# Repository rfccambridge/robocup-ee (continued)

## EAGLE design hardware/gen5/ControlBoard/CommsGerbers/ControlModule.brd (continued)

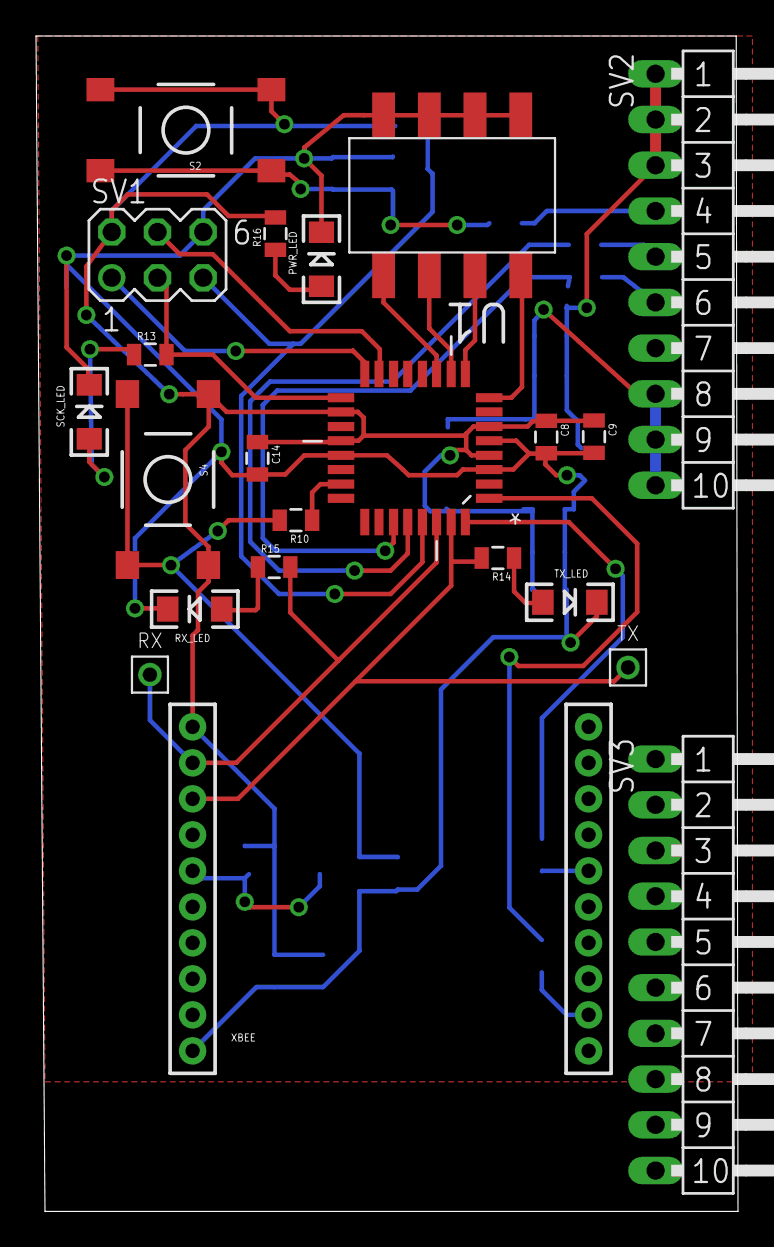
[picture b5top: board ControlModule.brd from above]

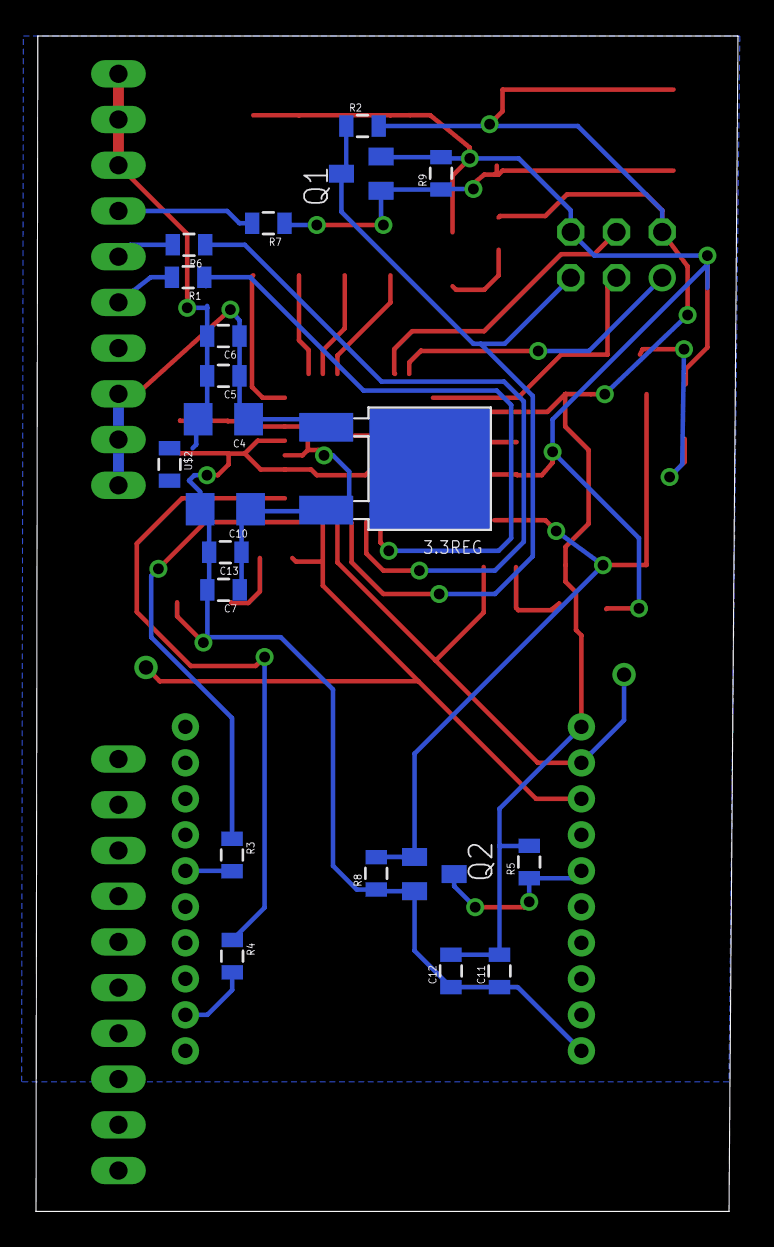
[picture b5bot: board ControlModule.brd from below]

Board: 2 copper layers, 39.0 x 65.3 mm, 44 parts (21 on the bottom side), 31 nets.

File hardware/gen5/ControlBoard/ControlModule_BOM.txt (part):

Partlist exported from C:/Users/joncr_000/robocup/robocup-ee/hardware/gen5/ControlBoard/ControlModule.sch at 12/26/2016 15:41:58

Part    Value         Device           Package               Description                                             MF MPN           OC_FARNELL OC_NEWARK PACKAGE PROD_ID    SUPPLIER VALUE        
3.3REG  3.3REG1AREG   3.3REG1AREG      DPAK                                                                                                                                                         
C4      47uF          CAP1206          1206                  Capacitor                                                                                                                              
C5      1uF           CAP0805          0805                  Capacitor                                                                                                                              
C6      0.01uF        CAP0805          0805                  Capacitor                                                                                                                              
C7      0.01uF        CAP0805          0805                  Capacitor                                                                                                                              
C8      10uF          CAP0805          0805                  Capacitor                                                                                                                              
C9      0.1uF         CAP0805          0805                  Capacitor                                                                                                                              
C10     47uF          CAP1206          1206                  Capacitor                                                                                                                              
C11     0.01uF        CAP0805          0805                  Capacitor                                                                                                                              
C12     1uF           CAP0805          0805                  Capacitor                                                                                                                              
C13     1uF           CAP0805          0805                  Capacitor                                                                                                                              
C14     0.1uF         CAP0805          0805                  Capacitor                                                                                                                              
FRAME1  FRAME-LETTER  FRAME-LETTER     CREATIVE_COMMONS      Schematic Frame                                                                                                                        
PWR_LED               LED1206          LED-1206              LEDs                                                                                                                                   
Q1      BSS123        BSS123           SOT23                 N-CHANNEL MOS FET                                                                                                                      
Q2      BSS123        BSS123           SOT23                 N-CHANNEL MOS FET                                                                                                                      
R1      100           RESISTOR0805-RES 0805                  Resistor                                                                                                                               
R2      10k           RESISTOR0805-RES 0805                  Resistor                                                                                                                               
R3      0             RESISTOR0805-RES 0805                  Resistor                                                                                                                               
R4      0             RESISTOR0805-RES 0805                  Resistor                                                                                                                               
R5      10k           RESISTOR0805-RES 0805                  Resistor                                                                                                                               
R6      100           RESISTOR0805-RES 0805                  Resistor                                                                                                                               
R7      100           RESISTOR0805-RES 0805                  Resistor                                                                                                                               
R8      10k           RESISTOR0805-RES 0805                  Resistor                                                                                                                               
R9      10k           RESISTOR0805-RES 0805                  Resistor                                                                                                                               
R10     100           RESISTOR0805-RES 0805                  Resistor                                                                                                                               
R13     1k            RESISTOR0805-RES 0805                  Resistor                                                                                                                               
R14     1k            RESISTOR0805-RES 0805                  Resistor                                                                                                                               
R15     1k            RESISTOR0805-RES 0805                  Resistor                                                                                                                               
R16     1k            RESISTOR0805-RES 0805                  Resistor                                                                                                                               
RX      TEST_PT       TEST_PT          TESTING_PT            Testing Point                                                                                                                          
RX_LED                LED1206          LED-1206              LEDs                                                                                                                                   
S2      TAC_SWITCHSMD TAC_SWITCHSMD    TACTILE-SWITCH-SMD    Momentary Switch                                                                                      SWCH-08247          TAC_SWITCHSMD
S4      TAC_SWITCHSMD TAC_SWITCHSMD    TACTILE-SWITCH-SMD    Momentary Switch                                                                                      SWCH-08247          TAC_SWITCHSMD
SCK_LED               LED1206          LED-1206              LEDs                                                                                                                                   
SV1     ICSP          MA03-2           MA03-2                PIN HEADER                                                               unknown    unknown                                            
SV2                   MA10-1W          MA10-1W               PIN HEADER                                                               unknown    unknown                                            
SV3                   MA10-1W          MA10-1W               PIN HEADER                                                               unknown    unknown                                            
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
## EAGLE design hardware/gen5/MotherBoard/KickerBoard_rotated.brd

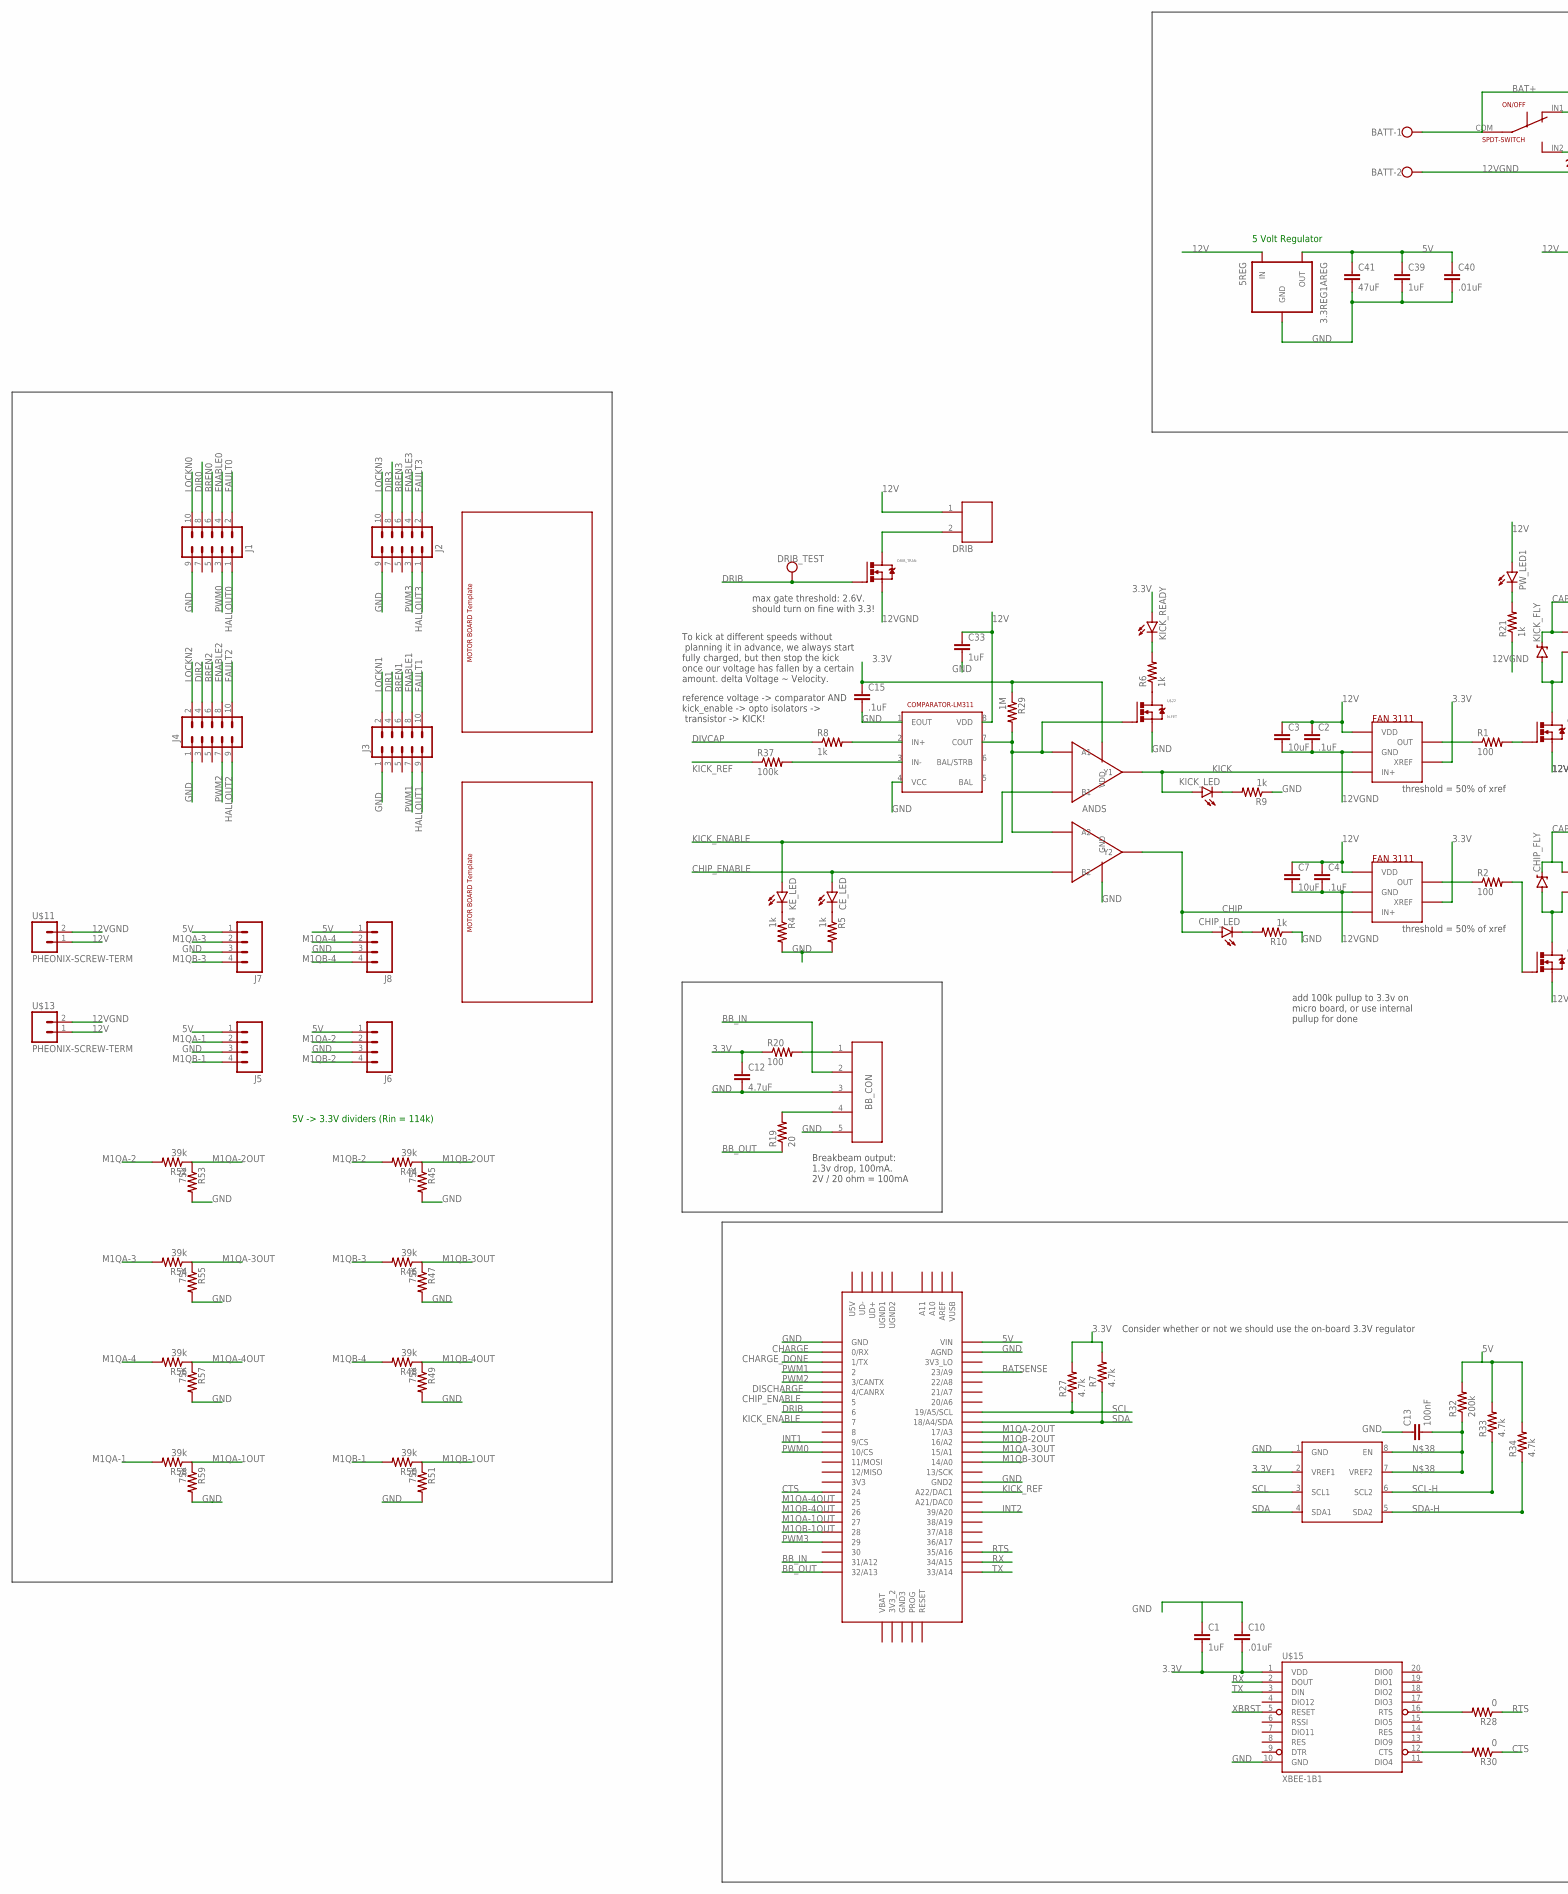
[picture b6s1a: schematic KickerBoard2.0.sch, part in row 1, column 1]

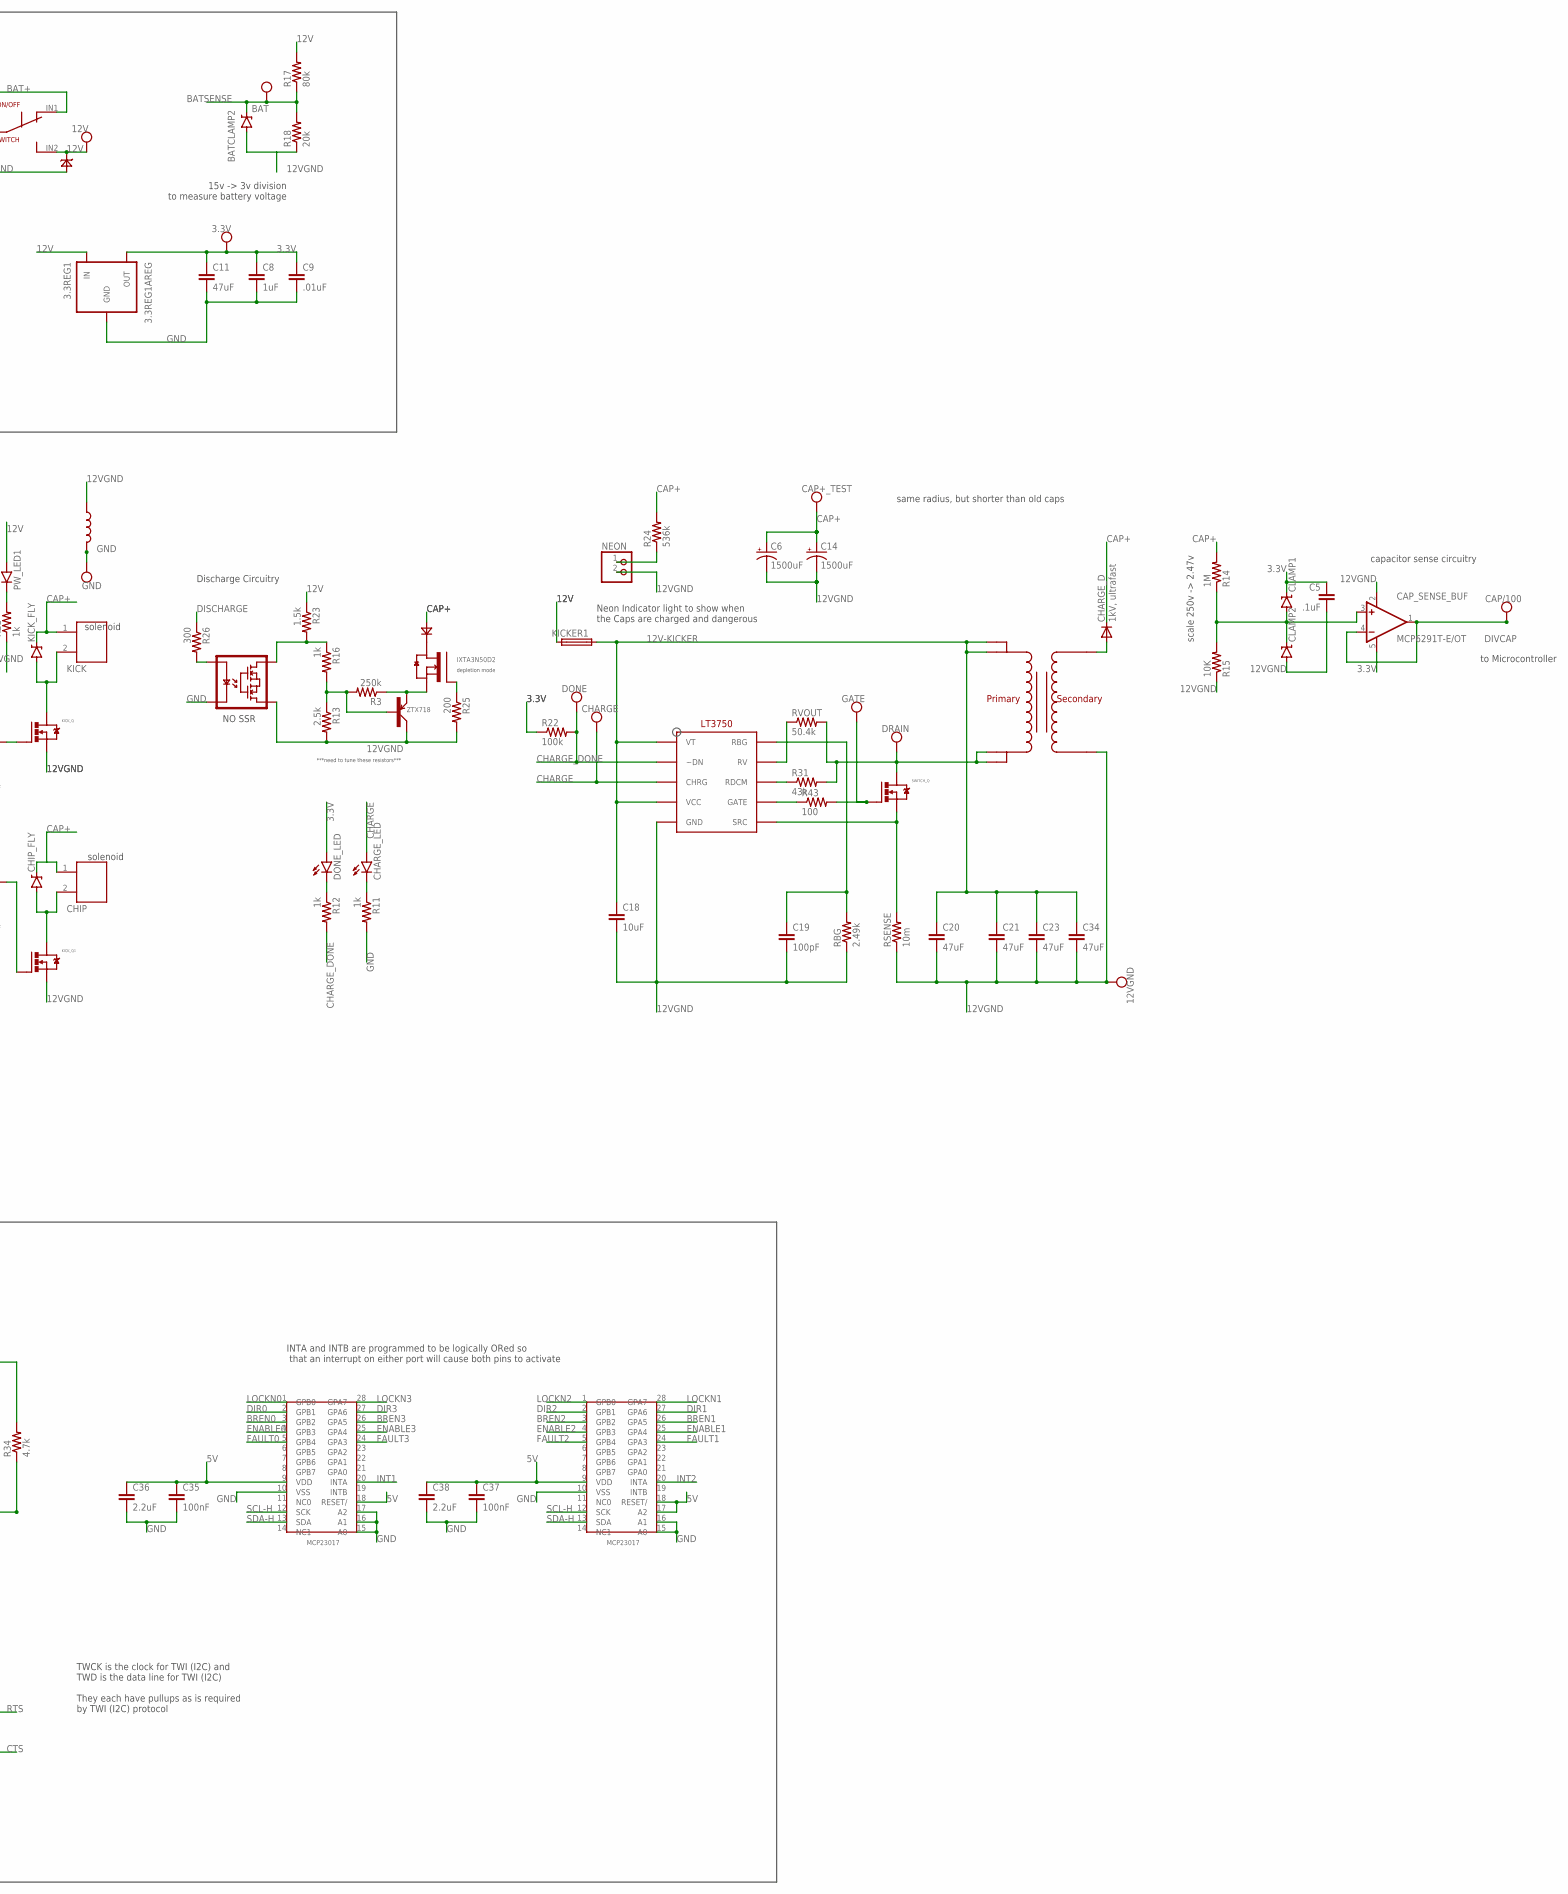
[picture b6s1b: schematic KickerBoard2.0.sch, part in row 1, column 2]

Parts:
3.3REG1, 5REG: 3.3REG1AREG; DPAK
3.3V, 12V, 12VGND: TEST_PT; TESTING_PT
ANDS: AND-DUAL; TSSOP8
BAT: TEST_PT; TESTING_PT
BATCLAMP2: DIODE-ZENERDO214AC; DO214AC
BATT: W237-102
BB_CON: JST-5; JST-5-2MM
C1, C33: 1uF; 1206
C2, C4: .1uF; 1206
C3, C7: 10uF; 1206
C5, C15: .1uF; 0805
C6, C14: 1500uF; EB35D
C8, C39: 1uF; 0805
C9, C40: .01uF; 0805
C10: .01uF; 1206
C11, C20, C21, C23, C34, C41: 47uF; 1206
C12: 4.7uF; 0805
C13, C35, C37: 100nF; 0805
C18: 10uF; 0805
C19: 100pF; 0805
C36, C38: 2.2uF; 0805
CAP+_TEST: TEST_PT; TESTING_PT
CAP/100: TEST_PT; TESTING_PT
CAP_SENSE_BUF: MCP6291T-E/OT; SOT23-5
CE_LED: LED1206; LED-1206
CHARGE: TEST_PT; TESTING_PT
CHARGE_D: 1kV, ultrafast; DO214AC
CHARGE_LED: LED1206; LED-1206
CHARGE_U: LT3750; 10-MSOP
CHIP: JST-22MM; JST-2-2MM
CHIP_FLY: DIODE-ZENERDO214AB; DO214AB
CHIP_LED: LED1206; LED-1206
CLAMP1, CLAMP2: DIODE-ZENERDO214AC; DO214AC
DONE: TEST_PT; TESTING_PT
DONE_LED: LED1206; LED-1206
DRAIN: TEST_PT; TESTING_PT
DRIB: JST-22MM; JST-2-2MM
DRIB_TEST: TEST_PT; TESTING_PT
DRIB_TRAN: N-MOSFETDPAK; DPAK
GATE: TEST_PT; TESTING_PT
GND: TEST_PT; TESTING_PT
J1, J2, J3, J4: M05X2SHD; 2X5-SHROUDED
J5, J6, J7, J8: M04PTH; 1X04
KE_LED: LED1206; LED-1206
KICK: JST-22MM; JST-2-2MM
KICKER1: TR5
KICK_FLY: DIODE-ZENERDO214AB; DO214AB
KICK_LED: LED1206; LED-1206
KICK_Q, KICK_Q1: N-MOSFETDPAK; DPAK
KICK_READY: LED1206; LED-1206
NEON: PINHD-1X2; 1X02
ON/OFF: SPDT-SWITCH; CK_SWITCH
PW_LED1: LED1206; LED-1206
R1, R2, R20, R43: 100; 0805
R3: 250k; 0805
R4, R5, R6, R8, R9, R10, R11, R12, R16, R21: 1k; 0805
R7, R27, R33, R34: 4.7k; 0805
R13: 2.5k; 0805
R14, R29: 1M; 0805
R15: 10K; 0805
R17: 80k; 0805
R18: 20k; 0805
R19: 20; 0805
R22, R37: 100k; 0805
R23: 1.5k; 0805
R24: 536k; 0805
R25: 200; 0805
R26: 300; 0805
R28, R30: 0; 0805
R31: 43k; 0805
R32: 200k; 0805
R44, R46, R48, R50, R52, R54, R56, R58: 39k; 0805
R45, R47, R49, R51, R53, R55, R57, R59: 75k; 0805
RBG: 2.49k; 0805
RSENSE: 10m; R2512
RVOUT: 50.4k; 0805
SWITCH_Q: N-MOSFETDPAK; DPAK
U$1, U$4: FAN31111; SOT23-5
U$2: IXTA3N50D2; TO-263
U$3: 32052-TRANSFORMER; 10-TRANSFORMER
U$5: VO1400AEFTR; SOP4
U$6: ZTX718; TO92
U$7: 1N4007; THROUGH-HOLE-2
U$8: PCA9306; SOIC8
U$9, U$10: MOTOR_BOARD
U$11, U$13: PHEONIX-SCREW-TERM; 1X02-PHEONIX
U$12: 13VZENER; THROUGH-HOLE-2
U$14: TEENSY_3.5/3.6
U$15: XBEE-1B1; XBEE-1
U$17, U$21: IO-EXPANDER; SSOP
U$18: LM311; SOIC8
U$19: INDUCTOR; 0805
U$22: N-FET; SOT-23

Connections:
3.3V: 3.3REG1.SOURCE (OUT), 3.3V.P$1, ANDS.P$8 (VDD), C1.2, C5.1, C8.1, C9.1, C10.2, C11.1, C12.1, C15.1, CAP_SENSE_BUF.5 (V+), CLAMP1.C, DONE_LED.A, KICK_READY.A, R7.2, R20.1, R22.1, R27.2, R29.1, U$1.4 (XREF), U$4.4 (XREF), U$8.2 (VREF1), U$15.1 (VDD)
5V: 5REG.SOURCE (OUT), C35.1, C36.1, C37.1, C38.1, C39.1, C40.1, C41.1, J5.1, J6.1, J7.1, J8.1, R32.2, R33.2, R34.2, U$14.VIN, U$17.9 (VDD), U$17.18 (RESET/), U$21.9 (VDD), U$21.17 (A2), U$21.18 (RESET/)
12V: 3.3REG1.GATE (IN), 5REG.GATE (IN), 12V.P$1, C2.1, C3.1, C4.1, C7.1, C33.1, DRIB.1, KICKER1.1, ON/OFF.IN2 (P2), PW_LED1.A, R17.2, R23.1, U$1.1 (VDD), U$4.1 (VDD), U$11.1, U$12.-, U$13.1, U$18.8 (VDD)
12V-KICKER: C18.1, C20.1, C21.1, C23.1, C34.1, CHARGE_U.P$1 (VT), CHARGE_U.P$4 (VCC), KICKER1.2, U$3.P$4, U$3.P$5
12VGND: 12VGND.P$1, BATCLAMP2.A, BATT.2, C2.2, C3.2, C4.2, C5.2, C6.-, C7.2, C14.-, C18.2, C19.2, C20.2, C21.2, C23.2, C34.2, CAP_SENSE_BUF.2 (V-), CHARGE_U.P$5 (GND), CLAMP2.A, DRIB_TRAN.SOURCE (S), KICK_Q.SOURCE (S), KICK_Q1.SOURCE (S), NEON.2, R13.2, R15.1, R18.1, R21.1, R25.2, RBG.1, RSENSE.1, U$1.2 (GND), U$3.P$10, U$4.2 (GND), U$5.3 (S2), U$6.LEFT (COLLECTOR), U$11.2, U$12.+, U$13.2, U$19.1
BAT+: BATT.1, ON/OFF.COM, ON/OFF.IN1 (P1)
BATSENSE: BAT.P$1, BATCLAMP2.C, R17.1, R18.2, U$14.23/A9
BB_IN: BB_CON.2, U$14.31/A12
BB_OUT: R19.1, U$14.32/A13
BREN0: J1.6, U$17.3 (GPB2)
BREN1: J3.6, U$21.26 (GPA5)
BREN2: J4.6, U$21.3 (GPB2)
BREN3: J2.6, U$17.26 (GPA5)
CAP+: C6.+, C14.+, CAP+_TEST.P$1, CHARGE_D.C, CHIP.1, CHIP_FLY.CATHODE (C), KICK.1, KICK_FLY.CATHODE (C), R14.2, R24.2, U$7.+ (D+)
CHARGE: CHARGE.P$1, CHARGE_LED.A, CHARGE_U.P$3 (CHRG), U$14.0/RX
CHARGE_DONE: CHARGE_U.P$2 (~DN), DONE.P$1, R12.2, R22.2, U$14.1/TX
CHIP: ANDS.P$3 (Y2), CHIP_LED.A, U$1.3 (IN+)
CHIP_ENABLE: ANDS.P$6 (B2), CE_LED.A, U$14.5
COMP_OUT: ANDS.P$1 (A1), ANDS.P$5 (A2), R29.2, U$18.7 (COUT), U$22.G
CTS: R30.1, U$14.24
DIR0: J1.8, U$17.2 (GPB1)
DIR1: J3.4, U$21.27 (GPA6)
DIR2: J4.4, U$21.2 (GPB1)
DIR3: J2.8, U$17.27 (GPA6)
DISCHARGE: R26.1, U$14.4/CANRX
DIVCAP: CAP/100.P$1, CAP_SENSE_BUF.1 (OUT), CAP_SENSE_BUF.4 (-IN), R8.1
DRIB: DRIB_TEST.P$1, DRIB_TRAN.GATE (G), U$14.6
ENABLE0: J1.4, U$17.4 (GPB3)
ENABLE1: J3.8, U$21.25 (GPA4)
ENABLE2: J4.8, U$21.4 (GPB3)
ENABLE3: J2.4, U$17.25 (GPA4)
FAULT0: J1.2, U$17.5 (GPB4)
FAULT1: J3.10, U$21.24 (GPA3)
FAULT2: J4.10, U$21.5 (GPB4)
FAULT3: J2.2, U$17.24 (GPA3)
GND: 3.3REG1.DRAIN (GND), 5REG.DRAIN (GND), ANDS.P$4 (GND), BB_CON.3, BB_CON.5, C8.2, C9.2, C10.1, C11.2, C12.2, C13.1, C15.2, C33.2, C35.2, C36.2, C37.2, C38.2, C39.2, C40.2, C41.2, GND.P$1, J1.9, J2.9, J3.1, J4.1, J5.3, J6.3, J7.3, J8.3, R4.2, R5.2, R9.1, R10.1, R11.2, R45.2, R47.2, R49.2, R51.2, R53.2, R55.2, R57.2, R59.2, U$5.2 (LED-), U$8.1 (GND), U$14.AGND, U$14.GND, U$14.GND2, U$15.10 (GND), U$17.10 (VSS), U$17.15 (A0), U$17.16 (A1), U$17.17 (A2), U$18.1 (EOUT), U$18.4 (VCC), U$19.2, U$21.10 (VSS), U$21.15 (A0), U$21.16 (A1), U$22.S
HALLOUT0: J1.1
HALLOUT1: J3.9
HALLOUT2: J4.9
HALLOUT3: J2.1
INT1: U$14.9/CS, U$17.20 (INTA)
INT2: U$14.39/A20, U$21.20 (INTA)
KICK: ANDS.P$7 (Y1), KICK_LED.A, U$4.3 (IN+)
KICK_ENABLE: ANDS.P$2 (B1), KE_LED.A, U$14.7
KICK_REF: R37.1, U$14.A22/DAC1
LOCKN0: J1.10, U$17.1 (GPB0)
LOCKN1: J3.2, U$21.28 (GPA7)
LOCKN2: J4.2, U$21.1 (GPB0)
LOCKN3: J2.10, U$17.28 (GPA7)
LOWCHIP: CHIP.2, CHIP_FLY.ANODE (A), KICK_Q1.DRAIN (D)
LOWKICK: KICK.2, KICK_FLY.ANODE (A), KICK_Q.DRAIN (D)
M1QA-1: J5.2, R58.2
M1QA-1OUT: R58.1, R59.1, U$14.27
M1QA-2: J6.2, R52.2
M1QA-2OUT: R52.1, R53.1, U$14.17/A3
M1QA-3: J7.2, R54.2
M1QA-3OUT: R54.1, R55.1, U$14.15/A1
M1QA-4: J8.2, R56.2
M1QA-4OUT: R56.1, R57.1, U$14.25
M1QB-1: J5.4, R50.2
M1QB-1OUT: R50.1, R51.1, U$14.28
M1QB-2: J6.4, R44.2
M1QB-2OUT: R44.1, R45.1, U$14.16/A2
M1QB-3: J7.4, R46.2
M1QB-3OUT: R46.1, R47.1, U$14.14/A0
M1QB-4: J8.4, R48.2
M1QB-4OUT: R48.1, R49.1, U$14.26
unnamed: DRAIN.P$1, R31.2, RVOUT.2, SWITCH_Q.DRAIN (D), U$3.P$6, U$3.P$7
unnamed: R1.1, U$4.5 (OUT)
unnamed: KICK_Q1.GATE (G), R2.2
unnamed: R28.2, U$15.16 (RTS)
unnamed: R2.1, U$1.5 (OUT)
unnamed: CHARGE_U.P$8 (RDCM), R31.1
unnamed: C19.1, CHARGE_U.P$10 (RBG), RBG.2
unnamed: KICK_Q.GATE (G), R1.2
unnamed: GATE.P$1, R43.2, SWITCH_Q.GATE (G)
unnamed: R3.1, U$2.LOWER_RIGHT (SOURCE), U$6.RIGHT (EMITTER)
unnamed: KE_LED.C, R4.1
unnamed: CHARGE_U.P$9 (RV), RVOUT.1
unnamed: CE_LED.C, R5.1
unnamed: R6.1, U$22.D
unnamed: KICK_LED.C, R9.2
unnamed: R30.2, U$15.12 (CTS)
unnamed: CHIP_LED.C, R10.2
unnamed: R3.2, R13.1, R16.2, U$6.CENTER (BASE)
unnamed: DONE_LED.C, R12.1
unnamed: CHARGE_LED.C, R11.1
unnamed: R25.1, U$2.LOWER_LEFT (GATE)
unnamed: PW_LED1.C, R21.2
unnamed: CHARGE_U.P$6 (SRC), RSENSE.2, SWITCH_Q.SOURCE (S)
unnamed: R16.1, R23.2, U$5.4 (S1)
unnamed: R26.2, U$5.1 (LED+)
unnamed: BB_CON.4, R19.2
unnamed: KICK_READY.C, R6.2
unnamed: CHARGE_U.P$7 (GATE), R43.1
unnamed: R8.2, U$18.2 (IN+)
unnamed: U$2.TAB (DRAIN), U$7.- (D-)
unnamed: C13.2, R32.1, U$8.7 (VREF2), U$8.8 (EN)
unnamed: BB_CON.1, R20.2
unnamed: R37.2, U$18.3 (IN-)
PWM0: J1.3, U$14.10/CS
PWM1: J3.7, U$14.2
PWM2: J4.7, U$14.3/CANTX
PWM3: J2.3, U$14.29
RTS: R28.1, U$14.35/A16
RX: U$14.34/A15, U$15.2 (DOUT)
SCL: R27.1, U$8.3 (SCL1), U$14.19/A5/SCL
SCL-H: R33.1, U$8.6 (SCL2), U$17.12 (SCK), U$21.12 (SCK)
SDA: R7.1, U$8.4 (SDA1), U$14.18/A4/SDA
SDA-H: R34.1, U$8.5 (SDA2), U$17.13 (SDA), U$21.13 (SDA)
TO_DRIB: DRIB.2, DRIB_TRAN.DRAIN (D)
TO_NEON: NEON.1, R24.1
TRANS_OUT: CHARGE_D.A, U$3.P$1
TX: U$14.33/A14, U$15.3 (DIN)
UNBUF_DIVCAP: CAP_SENSE_BUF.3 (+IN), CLAMP1.A, CLAMP2.C, R14.1, R15.2
XBRST: U$15.5 (RESET)

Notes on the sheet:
scale 250v -> 2.47v
To kick at different speeds without planning it in advance, we always start fully charged, but then stop the kick once our voltage has fallen by a certain amount. delta Voltage ~ Velocity.
reference voltage -> comparator AND kick_enable -> opto isolators -> transistor -> KICK!
add 100k pullup to 3.3v on micro board, or use internal pullup for done
Neon Indicator light to show when the Caps are charged and dangerous
to Microcontroller
threshold = 50% of xref
same radius, but shorter than old caps
Discharge Circuitry
capacitor sense circuitry
15v -> 3v division to measure battery voltage
max gate threshold: 2.6V. should turn on fine with 3.3!
Breakbeam output: 1.3v drop, 100mA. 2V / 20 ohm = 100mA
solenoid
IXTA3N50D2
ZTX718
***need to tune these resistors***
depletion mode
NO SSR
TWCK is the clock for TWI (I2C) and TWD is the data line for TWI (I2C) They each have pullups as is required by TWI (I2C) protocol
INTA and INTB are programmed to be logically ORed so that an interrupt on either port will cause both pins to activate
5 Volt Regulator
5V -> 3.3V dividers (Rin = 114k)
Consider whether or not we should use the on-board 3.3V regulator
